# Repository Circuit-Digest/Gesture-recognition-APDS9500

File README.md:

# DIY Gesture Recognition Module: Control Your Devices with a Wave

We have seen many types of control methods in electronic devices, including simple switches, rotary encoders, touch screens and even voice commands. Even though all of these methods work fine, we are always eager to try new methods for controlling our devices. One of which includes gesture recognition. Even the tech giant Google has been working on their own gesture recognition sensor named Project Soli. Inspired by that we have created our own gesture sensor. Our DIY module can be easily connected to a PC or Mac via a USB-C port, allowing you to control media playback, navigate applications, and perform any action that can be executed using a keyboard, all through intuitive gestures. 

For gesture sensing we are using the APDS-9500 sensor from Broadcom. It is an imaging-based gesture recognition IC with an I2C-bus interface. It can recognise nine gestures, including move up, move down, move left, move right, move forward, move backwards, circle-clockwise, circle-counterclockwise and wave. An RP2040 ARM SoC from the Raspberry Pi Foundation is being used as the main controller. When it is plugged in the RP2040 will enumerate an HID device and whenever a gesture is detected it will send a corresponding pre-programmed response to the PC using HID protocol. An ADM7171 ultra low noise LDO from Analog Devices is used for generating the 3.3V line for the SoC and the Sensor. To ensure the proper operation of the SoC we have also included an ADM803 voltage supervisor chip, which is also from Analog Devices.

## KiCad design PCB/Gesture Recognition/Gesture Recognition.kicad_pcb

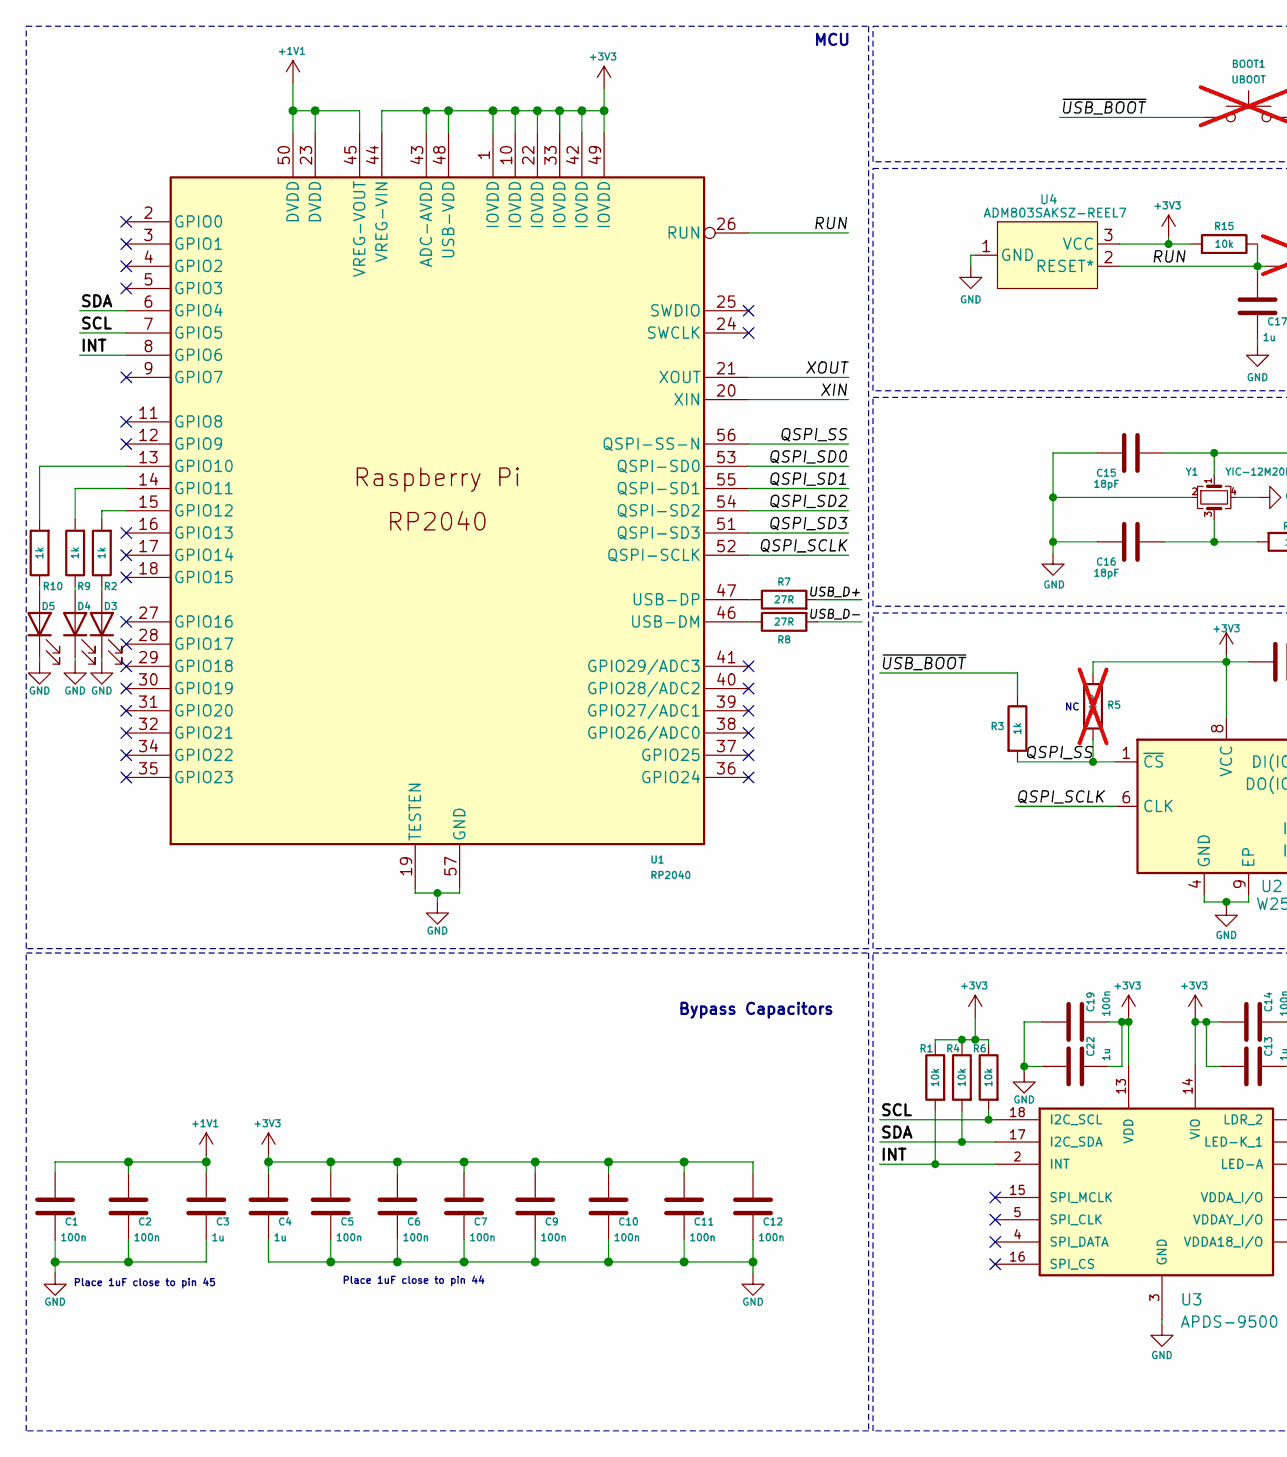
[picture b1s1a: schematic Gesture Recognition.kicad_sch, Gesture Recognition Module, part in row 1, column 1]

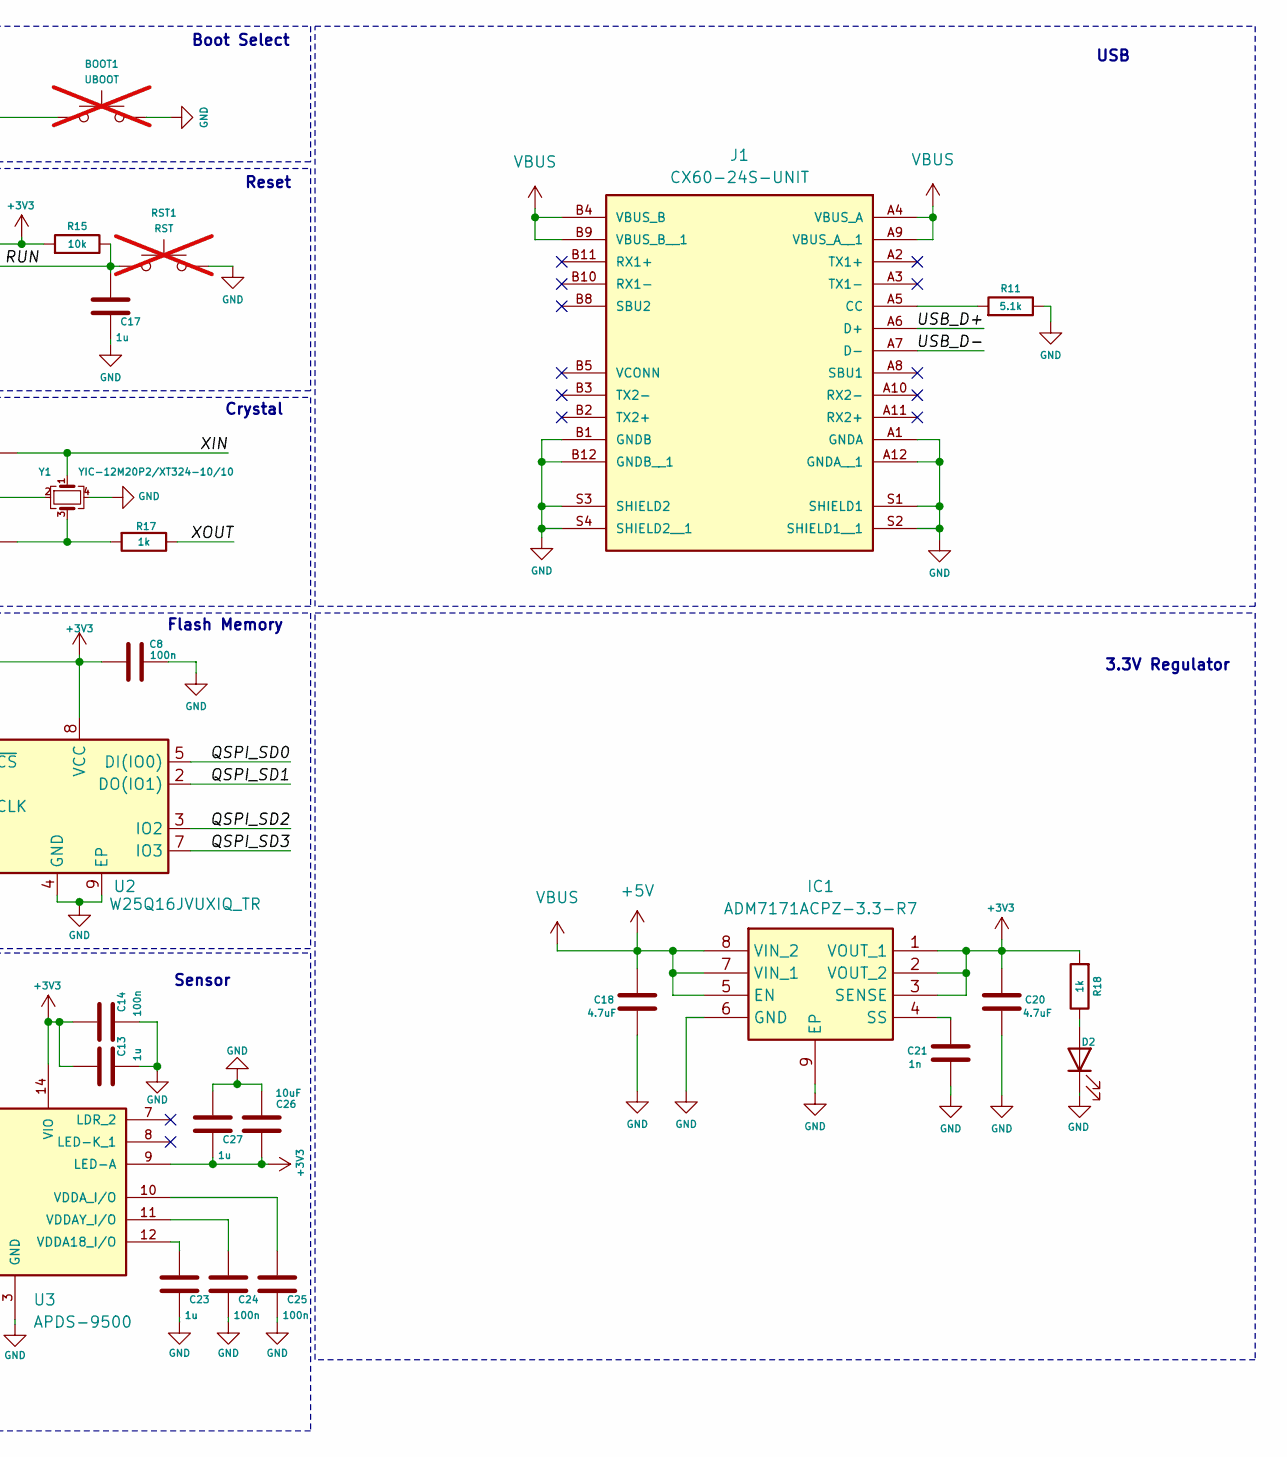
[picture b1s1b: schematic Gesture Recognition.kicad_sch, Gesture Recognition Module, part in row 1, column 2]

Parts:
BOOT1: UBOOT; R_0402_1005Metric; not fitted
C1, C2, C5, C6, C7, C8, C9, C10, C11, C12, C14, C19, C24, C25: 100n; C_0402_1005Metric; DigiKey Part Number 490-6328-1-ND
C3, C4, C13, C17, C22, C23, C27: 1u; C_0402_1005Metric; DigiKey Part Number 490-10018-1-ND
C15, C16: 18pF; C_0402_1005Metric; DigiKey Part Number 490-5858-1-ND
C18, C20: 4.7uF; C_0402_1005Metric; DigiKey Part Number 1276-1482-1-ND
C21: 1n; C_0402_1005Metric; DigiKey Part Number 490-3244-1-ND
C26: 10uF; C_0402_1005Metric; DigiKey Part Number 490-GRM155R60J106ME05DCT-ND
D2, D5: LED Red; LED_0402_1005Metric; DigiKey Part Number 3147-B2841USD-20D001014U1930CT-ND
D3: LED Green; LED_0402_1005Metric; DigiKey Part Number 3147-B2841NG--05D000514U1930CT-ND
D4: LED Blue; LED_0402_1005Metric; DigiKey Part Number 3147-B2841NB--20C001414U1930CT-ND
IC1: ADM7171ACPZ-3.3-R7; SON50P300X300X80-9N-D; DigiKey Part Number 505-ADM7171ACPZ-3.3-R7CT-ND
J1: CX60-24S-UNIT; HIROSE_CX60-24S-UNIT; PARTREV 5; DigiKey Part Number H126317-ND
R1, R4, R6, R15: 10k; R_0402_1005Metric; DigiKey Part Number P10.0KLCT-ND
R2, R3, R9, R10, R17, R18: 1k; R_0402_1005Metric; DigiKey Part Number P1.00KLCT-ND
R5: DNP; R_0402_1005Metric; not fitted
R7, R8: 27R; R_0402_1005Metric; DigiKey Part Number P27.0LCT-ND
R11: 5.1k; R_0402_1005Metric; DigiKey Part Number P5.1KJCT-ND
RST1: RST; R_0402_1005Metric; not fitted
U1: RP2040; RP2040-QFN-56; DigiKey Part Number 2648-SC0914(13)CT-ND
U2: W25Q16JVUXIQ_TR; SON50P300X200X60-9N; DigiKey Part Number 256-W25Q16JVUXIQTRCT-ND
U3: APDS-9500; ADPS-9500; DigiKey Part Number 516-3579-1-ND
U4: ADM803SAKSZ-REEL7; KS_3_ADI; DigiKey Part Number 505-ADM803SAKSZ-REEL7CT-ND
Y1: YIC-12M20P2/XT324-10/10; Crystal_SMD_3225-4Pin_3.2x2.5mm; DigiKey Part Number 2151-RH100-12.000-18-2030-EXT-TRCT-ND

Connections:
+1V1: C1.1, C2.1, C3.1, U1.23 (DVDD), U1.45 (VREG-VOUT), U1.50 (DVDD)
+3V3: C4.1, C5.1, C6.1, C7.1, C8.1, C9.1, C10.1, C11.1, C12.1, C13.1, C14.1, C19.2, C20.2, C22.2, C26.1, C27.2, IC1.1 (VOUT_1), IC1.2 (VOUT_2), IC1.3 (SENSE), R1.1, R4.1, R5.1, R6.1, R15.2, R18.2, U1.1 (IOVDD), U1.10 (IOVDD), U1.22 (IOVDD), U1.33 (IOVDD), U1.42 (IOVDD), U1.43 (ADC-AVDD), U1.44 (VREG-VIN), U1.48 (USB-VDD), U1.49 (IOVDD), U2.8 (VCC), U3.9 (LED-A), U3.13 (VDD), U3.14 (VIO), U4.3 (VCC)
+5V: C18.2, IC1.5 (EN), IC1.7 (VIN_1), IC1.8 (VIN_2), J1.A4 (VBUS_A), J1.A9 (VBUS_A__1), J1.B4 (VBUS_B), J1.B9 (VBUS_B__1)
/INT: R1.2, U1.8 (GPIO6), U3.2 (INT)
/QSPI_SCLK: U1.52 (QSPI-SCLK), U2.6 (CLK)
/QSPI_SD0: U1.53 (QSPI-SD0), U2.5 (DI(IO0))
/QSPI_SD1: U1.55 (QSPI-SD1), U2.2 (DO(IO1))
/QSPI_SD2: U1.54 (QSPI-SD2), U2.3 (IO2)
/QSPI_SD3: U1.51 (QSPI-SD3), U2.7 (IO3)
/QSPI_SS: R3.2, R5.2, U1.56 (QSPI-SS-N), U2.1 (~CS)
/RUN: C17.1, R15.1, RST1.1, U1.26 (RUN), U4.2 (RESET*)
/SCL: R6.2, U1.7 (GPIO5), U3.18 (I2C_SCL)
/SDA: R4.2, U1.6 (GPIO4), U3.17 (I2C_SDA)
/USB_D+: J1.A6 (D+), R7.2
/USB_D-: J1.A7 (D-), R8.2
/XIN: C15.1, U1.20 (XIN), Y1.1
/XOUT: R17.1, U1.21 (XOUT)
/~USB_BOOT: BOOT1.1, R3.1
GND: BOOT1.2, C1.2, C2.2, C3.2, C4.2, C5.2, C6.2, C7.2, C8.2, C9.2, C10.2, C11.2, C12.2, C13.2, C14.2, C15.2, C16.2, C17.2, C18.1, C19.1, C20.1, C21.1, C22.1, C23.2, C24.2, C25.2, C26.2, C27.1, D2.1 (K), D3.1 (K), D4.1 (K), D5.1 (K), IC1.6 (GND), IC1.9 (EP), J1.A1 (GNDA), J1.A12 (GNDA__1), J1.B1 (GNDB), J1.B12 (GNDB__1), J1.S1 (SHIELD1), J1.S2 (SHIELD1__1), J1.S3 (SHIELD2), J1.S4 (SHIELD2__1), R11.1, RST1.2, U1.19 (TESTEN), U1.57 (GND), U2.4 (GND), U2.9 (EP), U3.3 (GND), U4.1 (GND), Y1.2, Y1.4
unnamed: C16.1, R17.2, Y1.3
unnamed: D2.2 (A), R18.1
unnamed: D3.2 (A), R2.1
unnamed: D4.2 (A), R9.1
unnamed: D5.2 (A), R10.1
unnamed: C21.2, IC1.4 (SS)
unnamed: J1.A5 (CC), R11.2
unnamed: R10.2, U1.13 (GPIO10)
unnamed: R9.2, U1.14 (GPIO11)
unnamed: R2.2, U1.15 (GPIO12)
unnamed: R8.1, U1.46 (USB-DM)
unnamed: R7.1, U1.47 (USB-DP)
unnamed: C23.1, U3.12 (VDDA18_I/O)
unnamed: C24.1, U3.11 (VDDAY_I/O)
unnamed: C25.1, U3.10 (VDDA_I/O)

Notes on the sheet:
Reset
MCU
Place 1uF close to pin 45
Crystal
USB
Flash Memory
Boot Select
Place 1uF close to pin 44
Sensor
3.3V Regulator
Bypass Capacitors

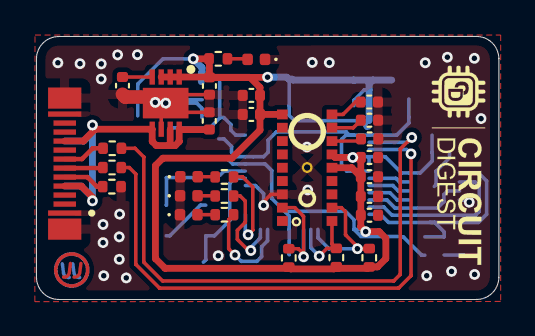
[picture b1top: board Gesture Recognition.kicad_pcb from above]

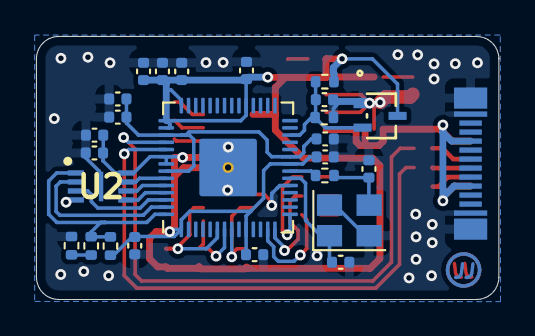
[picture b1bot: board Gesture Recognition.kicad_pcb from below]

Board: 2 copper layers, 25.7 x 14.6 mm, 54 parts (25 on the bottom side), 34 nets.

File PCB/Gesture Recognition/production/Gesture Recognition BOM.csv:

"Reference","Value","Datasheet","Footprint","Qty","DNP","DigiKey Link","DigiKey Part Number","Manufacturer","Manufacturer Product Number"
"BOOT1","UBOOT","~","Resistor_SMD:R_0402_1005Metric","1","DNP","","","",""
"C1,C2,C5,C6,C7,C8,C9,C10,C11,C12,C14,C19,C24,C25","100n","~","Capacitor_SMD:C_0402_1005Metric","14","","https://www.digikey.in/en/products/detail/murata-electronics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","490-6328-1-ND","Murata Electronics","GRM155R71C104KA88J"
"C3,C4,C13,C17,C22,C23,C27","1u","~","Capacitor_SMD:C_0402_1005Metric","7","","https://www.digikey.in/en/products/detail/murata-electronics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","490-10018-1-ND","Murata Electronics","GRM155R61E105MA12D"
"C15,C16","18pF","~","Capacitor_SMD:C_0402_1005Metric","2","","https://www.digikey.in/en/products/detail/murata-electronics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","490-5858-1-ND","Murata Electronics","GRM1555C1H180JA01D"
"C18,C20","4.7uF","~","Capacitor_SMD:C_0402_1005Metric","2","","https://www.digikey.in/en/products/detail/samsung-electro-me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","1276-1482-1-ND","Samsung Electro-Mechanics","CL05A475MP5NRNC"
"C21","1n","~","Capacitor_SMD:C_0402_1005Metric","1","","https://www.digikey.in/en/products/detail/murata-electronics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","490-3244-1-ND","Murata Electronics","GRM1555C1H102JA01D"
"C26","10uF","~","Capacitor_SMD:C_0402_1005Metric","1","","https://www.digikey.in/en/products/detail/murata-electronics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","490-GRM155R60J106ME05DCT-ND","Manufacturer","GRM155R60J106ME05D"
"D2,D5","LED Red","~","LED_SMD:LED_0402_1005Metric","2","","https://www.digikey.in/en/products/detail/harvatek-corporati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","3147-B2841USD-20D001014U1930CT-ND","Harvatek Corporation","B2841USD-20D001014U1930"
"D3","LED Green","~","LED_SMD:LED_0402_1005Metric","1","","https://www.digikey.in/en/products/detail/harvatek-corporati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","3147-B2841NG--05D000514U1930CT-ND","Harvatek Corporation","B2841NG--05D000514U1930"
"D4","LED Blue","~","LED_SMD:LED_0402_1005Metric","1","","https://www.digikey.in/en/products/detail/harvatek-corporati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","3147-B2841NB--20C001414U1930CT-ND","Harvatek Corporation","B2841NB--20C001414U1930"
"IC1","ADM7171ACPZ-3.3-R7","http://www.analog.com/media/en/technical-documentation/data-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","ADM7171ACPZ-3.3-R7:SON50P300X300X80-9N-D","1","","https://www.digikey.in/en/products/detail/analog-devices-inc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","505-ADM7171ACPZ-3.3-R7CT-ND","Analog Devices","ADM7171ACPZ-3.3-R7"
"J1","CX60-24S-UNIT","","CX60_24S_UNIT:HIROSE_CX60-24S-UNIT","1","","https://www.digikey.in/en/products/detail/hirose-electric-co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","H126317-ND","Hirose Electric Co Ltd","CX60-24S-UNIT"
"R1,R4,R6,R15","10k","~","Resistor_SMD:R_0402_1005Metric","4","","https://www.digikey.in/en/products/detail/panasonic-electron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","P10.0KLCT-ND","Panasonic Electronic Components","ERJ-2RKF1002X"
"R2,R3,R9,R10,R17,R18","1k","~","Resistor_SMD:R_0402_1005Metric","6","","https://www.digikey.in/en/products/detail/panasonic-electron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","P1.00KLCT-ND","Panasonic Electronic Components","ERJ-2RKF1001X"
"R5","DNP","~","Resistor_SMD:R_0402_1005Metric","1","DNP","","","",""
"R7,R8","27R","~","Resistor_SMD:R_0402_1005Metric","2","","https://www.digikey.in/en/products/detail/panasonic-electron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","P27.0LCT-ND","Panasonic Electronic Components","ERJ-2RKF27R0X"
"R11","5.1k","~","Resistor_SMD:R_0402_1005Metric","1","","https://www.digikey.in/en/products/detail/panasonic-electron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","P5.1KJCT-ND","Panasonic Electronic Components","ERJ-2GEJ512X"
"RST1","RST","~","Resistor_SMD:R_0402_1005Metric","1","DNP","","","",""
"U1","RP2040","https://datasheets.raspberrypi.org/rp2040/rp2040-datasheet.pdf","RP2040:RP2040-QFN-56","1","","https://www.digikey.in/en/products/detail/raspberry-pi/SC091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","2648-SC0914(13)CT-ND","Raspberry Pi","SC0914(13)"
"U2","W25Q16JVUXIQ_TR","https://componentsearchengine.com/Datasheets/1/W25Q16JVUXIQ TR.pdf","SON50P300X200X60-9N","1","","https://www.digikey.in/en/products/detail/winbond-electronic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","256-W25Q16JVUXIQTRCT-ND","Winbond",""
"U3","APDS-9500","","APDS-9500:ADPS-9500","1","","https://www.digikey.in/en/products/detail/broadcom-limited/A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","516-3579-1-ND","Broadcom Limited","APDS-9500"
"U4","ADM803SAKSZ-REEL7","ADM803SAKSZ-REEL7","ADM803SAKSZ:KS_3_ADI","1","","https://www.digikey.in/en/products/detail/analog-devices-inc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","505-ADM803SAKSZ-REEL7CT-ND","Analog Devices Inc.","ADM803SAKSZ-REEL7"
"Y1","YIC-12M20P2/XT324-10/10","~","Crystal:Crystal_SMD_3225-4Pin_3.2x2.5mm","1","","https://www.digikey.in/en/products/detail/raltron-electronic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","2151-RH100-12.000-18-2030-EXT-TRCT-ND","Raltron Electronics","RH100-12.000-18-2030-EXT-TR"

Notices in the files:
parts and their libraries:
License: CC BY 4.0
